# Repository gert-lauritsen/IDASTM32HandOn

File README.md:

På dette seminar vil vi sætte dig i gang med STM32. Vi ser på de værktøjer, du skal bruge for at komme i gang. Det hele er gratis, så det er bare med at komme i gang. Vi gennemgår alle basale hardwaredele, så du nemt kan komme videre. Der bliver nogle hands-on-opgaver, så tag din bærbare computer med.

Agenda

* Grafisk opsætning
* Debugger
* Seriel kommunikation (uart)
* SPI
* Timer
* ADC
* USB (virtuel comport)

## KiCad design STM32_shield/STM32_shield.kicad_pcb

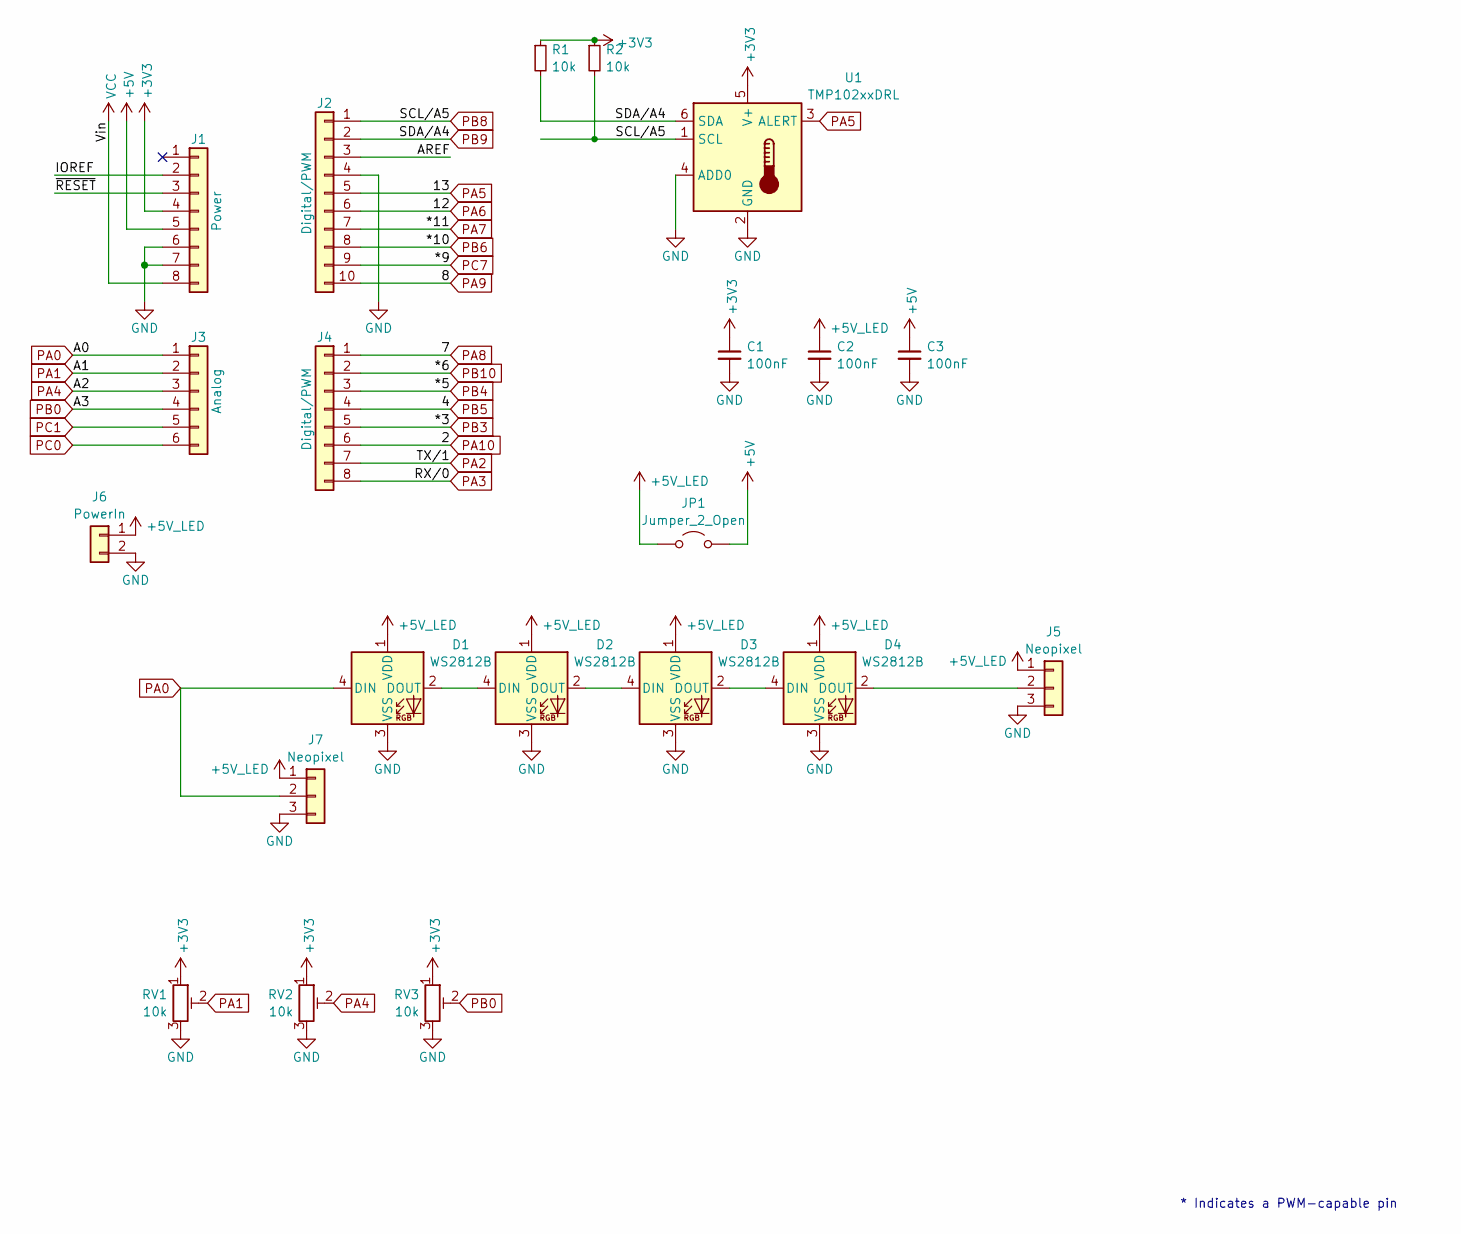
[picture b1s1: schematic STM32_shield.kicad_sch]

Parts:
C1, C2, C3: 100nF; C_0805_2012Metric
D1, D2, D3, D4: WS2812B; LED_WS2812B_PLCC4_5.0x5.0mm_P3.2mm; LCSC C114587
J1: Power; PinSocket_1x08_P2.54mm_Vertical
J2: Digital/PWM; PinSocket_1x10_P2.54mm_Vertical
J3: Analog; PinSocket_1x06_P2.54mm_Vertical
J4: Digital/PWM; PinSocket_1x08_P2.54mm_Vertical
J5, J7: Neopixel; PinSocket_1x03_P2.54mm_Vertical
J6: PowerIn; PhoenixContact_MSTBVA_2,5_2-G_1x02_P5.00mm_Vertical
JP1: Jumper_2_Open; SolderJumper-2_P1.3mm_Open_RoundedPad1.0x1.5mm
R1, R2: 10k; R_0805_2012Metric
RV1, RV2, RV3: 10k; Potentiometer_Runtron_RM-065_Vertical
U1: TMP102xxDRL; SOT-563; LCSC C99269

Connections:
+3V3: C1.1, J1.4, R1.1, R2.1, RV1.1, RV2.1, RV3.1, U1.5 (V+)
+5V: C3.1, J1.5, JP1.2 (B)
+5V_LED: C2.1, D1.1 (VDD), D2.1 (VDD), D3.1 (VDD), D4.1 (VDD), J5.1, J6.1, J7.1, JP1.1 (A)
/AREF: J2.3
/IOREF: J1.2
/~RESET: J1.3
GND: C1.2, C2.2, C3.2, D1.3 (VSS), D2.3 (VSS), D3.3 (VSS), D4.3 (VSS), J1.6, J1.7, J2.4, J5.3, J6.2, J7.3, RV1.3, RV2.3, RV3.3, U1.2 (GND), U1.4 (ADD0)
unnamed: D1.2 (DOUT), D2.4 (DIN)
unnamed: D2.2 (DOUT), D3.4 (DIN)
unnamed: D3.2 (DOUT), D4.4 (DIN)
unnamed: D4.2 (DOUT), J5.2
PA0: D1.4 (DIN), J3.1, J7.2
PA1: J3.2, RV1.2
PA2: J4.7
PA3: J4.8
PA4: J3.3, RV2.2
PA5: J2.5, U1.3 (ALERT)
PA6: J2.6
PA7: J2.7
PA8: J4.1
PA9: J2.10
PA10: J4.6
PB0: J3.4, RV3.2
PB3: J4.5
PB4: J4.3
PB5: J4.4
PB6: J2.8
PB8: J2.1, R2.2, U1.1 (SCL)
PB9: J2.2, R1.2, U1.6 (SDA)
PB10: J4.2
PC0: J3.6
PC1: J3.5
PC7: J2.9
VCC: J1.8

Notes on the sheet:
* Indicates a PWM-capable pin

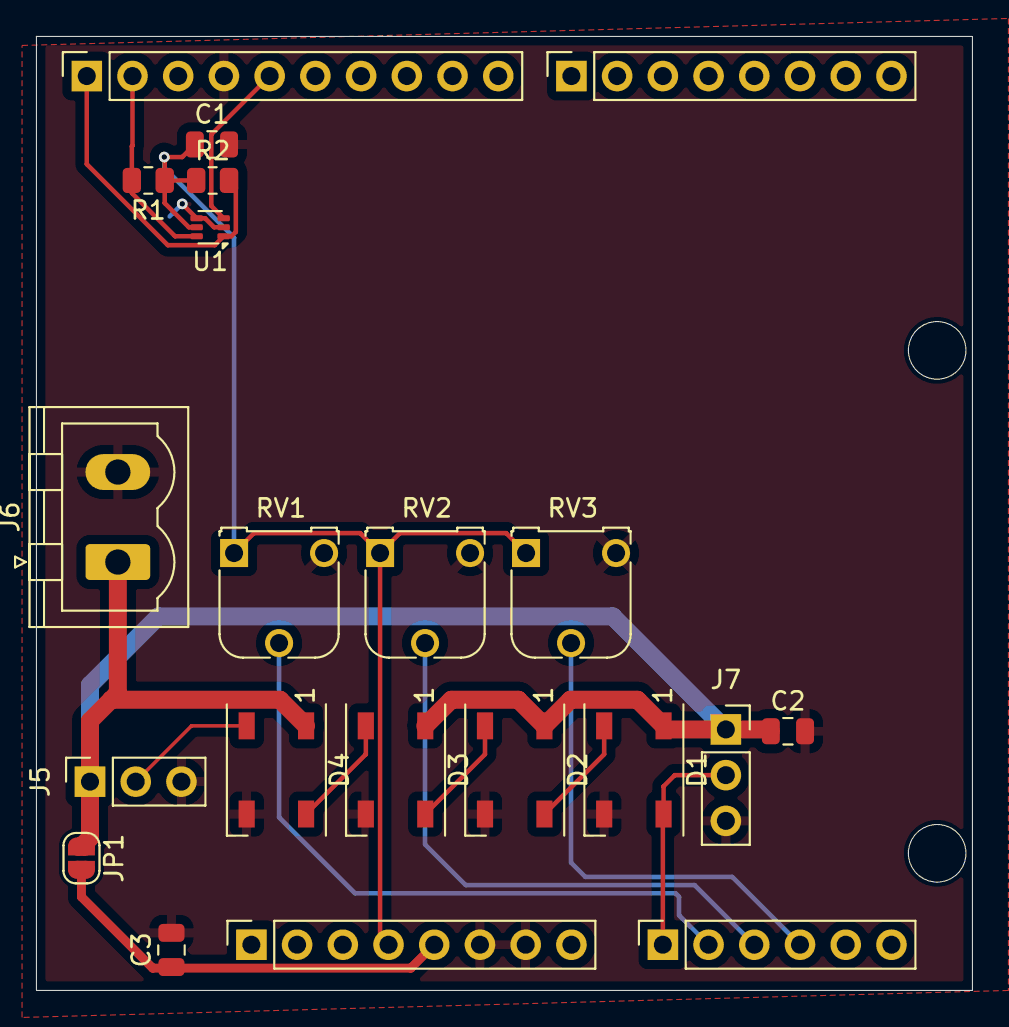
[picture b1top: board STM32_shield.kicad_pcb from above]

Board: 2 copper layers, 52.0 x 53.0 mm, 23 parts (0 on the bottom side), 15 nets.

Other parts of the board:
MH3, MH4: MountingHole_3.2mm

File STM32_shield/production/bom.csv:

Designator,Footprint,Quantity,Value,LCSC Part #
"C1, C2, C3",0805,3,100nF,
"D1, D2, D3, D4",LED_WS2812B_PLCC4_5.0x5.0mm_P3.2mm,4,WS2812B,C114587
J1,PinSocket_1x08_P2.54mm_Vertical,1,Power,
J2,PinSocket_1x10_P2.54mm_Vertical,1,Digital/PWM,
J3,PinSocket_1x06_P2.54mm_Vertical,1,Analog,
J4,PinSocket_1x08_P2.54mm_Vertical,1,Digital/PWM,
"J5, J7",PinSocket_1x03_P2.54mm_Vertical,2,Neopixel,
J6,"PhoenixContact_MSTBVA_2,5_2-G_1x02_P5.00mm_Vertical",1,PowerIn,
JP1,SolderJumper-2_P1.3mm_Open_RoundedPad1.0x1.5mm,1,Jumper_2_Open,
"R1, R2",0805,2,10k,
"RV1, RV2, RV3",Potentiometer_Runtron_RM-065_Vertical,3,10k,
U1,SOT-563,1,TMP102xxDRL,C99269

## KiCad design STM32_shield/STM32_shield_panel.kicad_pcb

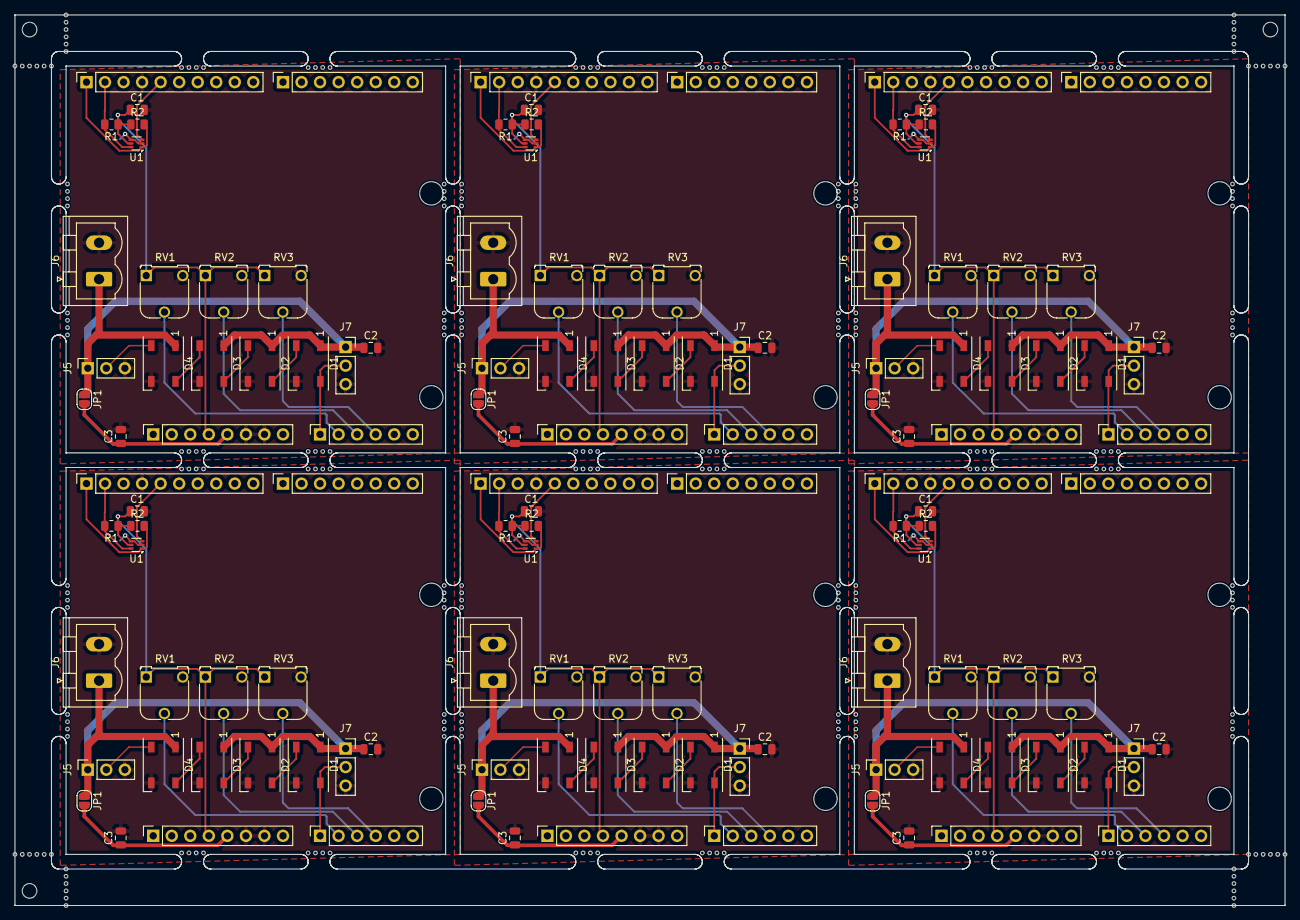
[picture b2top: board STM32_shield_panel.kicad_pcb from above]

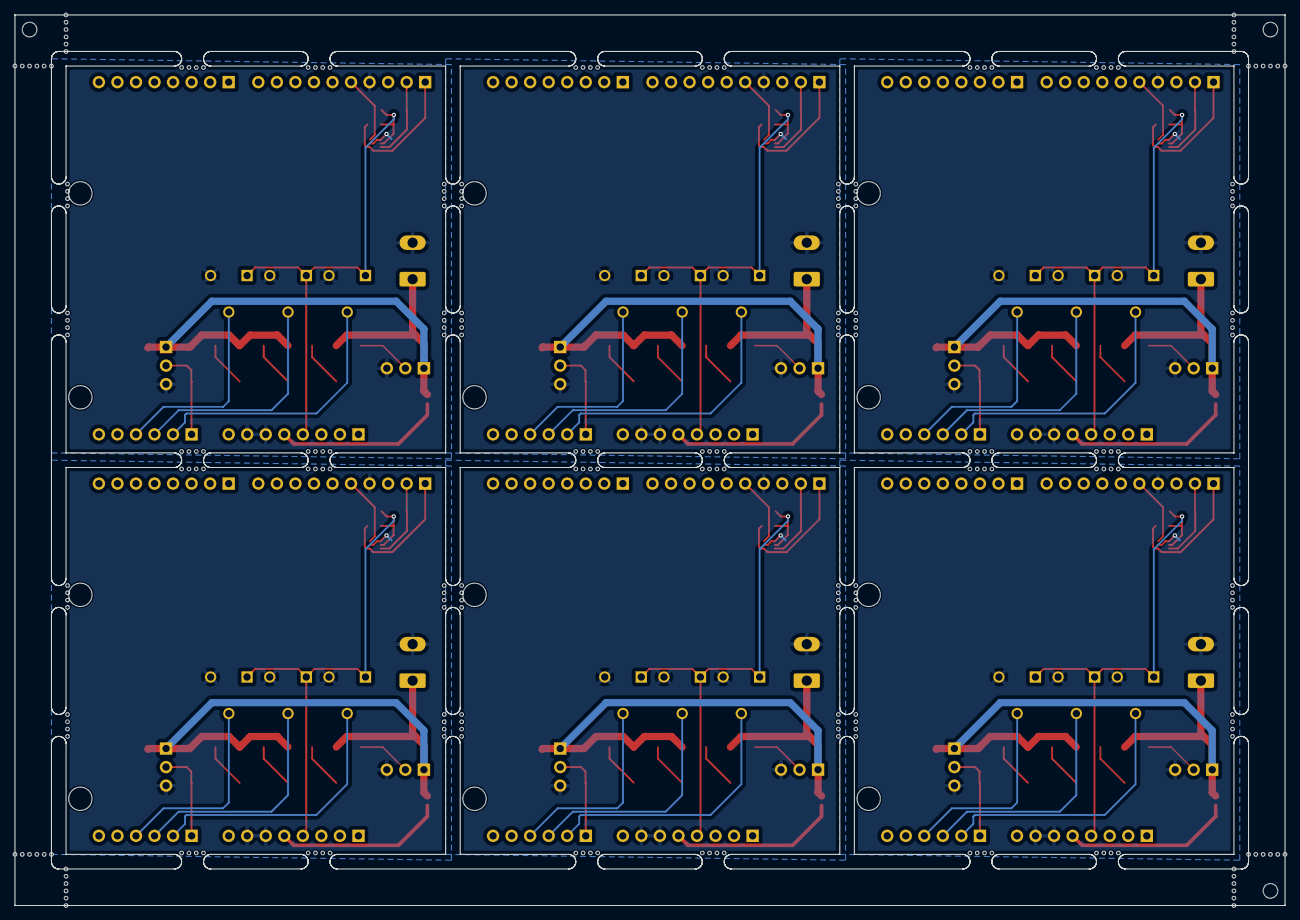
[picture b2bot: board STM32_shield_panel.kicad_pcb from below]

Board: 2 copper layers, 174.0 x 122.0 mm, 387 parts (3 on the bottom side), 90 nets.

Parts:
C1, C1#2, C1#3, C1#4, C1#5, C1#6, C2, C2#2, C2#3, C2#4, C2#5, C2#6, C3, C3#2, C3#3, C3#4, C3#5, C3#6: 100nF; C_0805_2012Metric
D1, D1#2, D1#3, D1#4, D1#5, D1#6, D2, D2#2, D2#3, D2#4, D2#5, D2#6, D3, D3#2, D3#3, D3#4, D3#5, D3#6, D4, D4#2, D4#3, D4#4, D4#5, D4#6: WS2812B; LED_WS2812B_PLCC4_5.0x5.0mm_P3.2mm
J1, J1#2, J1#3, J1#4, J1#5, J1#6: Power; PinSocket_1x08_P2.54mm_Vertical
J2, J2#2, J2#3, J2#4, J2#5, J2#6: Digital/PWM; PinSocket_1x10_P2.54mm_Vertical
J3, J3#2, J3#3, J3#4, J3#5, J3#6: Analog; PinSocket_1x06_P2.54mm_Vertical
J4, J4#2, J4#3, J4#4, J4#5, J4#6: Digital/PWM; PinSocket_1x08_P2.54mm_Vertical
J5, J5#2, J5#3, J5#4, J5#5, J5#6, J7, J7#2, J7#3, J7#4, J7#5, J7#6: Neopixel; PinSocket_1x03_P2.54mm_Vertical
J6, J6#2, J6#3, J6#4, J6#5, J6#6: PowerIn; PhoenixContact_MSTBVA_2,5_2-G_1x02_P5.00mm_Vertical
JP1, JP1#2, JP1#3, JP1#4, JP1#5, JP1#6: Jumper_2_Open; SolderJumper-2_P1.3mm_Open_RoundedPad1.0x1.5mm
KiKit_FID_B_1, KiKit_FID_B_2, KiKit_FID_B_3: Fiducial
KiKit_FID_T_1, KiKit_FID_T_2, KiKit_FID_T_3: Fiducial
KiKit_MB_1_1, KiKit_MB_1_2, KiKit_MB_1_3, KiKit_MB_1_4, KiKit_MB_2_1, KiKit_MB_2_2, KiKit_MB_2_3, KiKit_MB_2_4, KiKit_MB_3_1, KiKit_MB_3_2, KiKit_MB_3_3, KiKit_MB_3_4, KiKit_MB_4_1, KiKit_MB_4_2, KiKit_MB_4_3, KiKit_MB_4_4, KiKit_MB_5_1, KiKit_MB_5_2, KiKit_MB_5_3, KiKit_MB_5_4, KiKit_MB_6_1, KiKit_MB_6_2, KiKit_MB_6_3, KiKit_MB_6_4, KiKit_MB_7_1, KiKit_MB_7_2, KiKit_MB_7_3, KiKit_MB_7_4, KiKit_MB_8_1, KiKit_MB_8_2, KiKit_MB_8_3, KiKit_MB_8_4, KiKit_MB_9_1, KiKit_MB_9_2, KiKit_MB_9_3, KiKit_MB_9_4, KiKit_MB_10_1, KiKit_MB_10_2, KiKit_MB_10_3, KiKit_MB_10_4, KiKit_MB_11_1, KiKit_MB_11_2, KiKit_MB_11_3, KiKit_MB_11_4, KiKit_MB_12_1, KiKit_MB_12_2, KiKit_MB_12_3, KiKit_MB_12_4, KiKit_MB_13_1, KiKit_MB_13_2, KiKit_MB_13_3, KiKit_MB_13_4, KiKit_MB_14_1, KiKit_MB_14_2, KiKit_MB_14_3, KiKit_MB_14_4, KiKit_MB_15_1, KiKit_MB_15_2, KiKit_MB_15_3, KiKit_MB_15_4, KiKit_MB_16_1, KiKit_MB_16_2, KiKit_MB_16_3, KiKit_MB_16_4, KiKit_MB_17_1, KiKit_MB_17_2, KiKit_MB_17_3, KiKit_MB_17_4, KiKit_MB_18_1, KiKit_MB_18_2, KiKit_MB_18_3, KiKit_MB_18_4, KiKit_MB_19_1, KiKit_MB_19_2, KiKit_MB_19_3, KiKit_MB_19_4, KiKit_MB_20_1, KiKit_MB_20_2, KiKit_MB_20_3, KiKit_MB_20_4, KiKit_MB_21_1, KiKit_MB_21_2, KiKit_MB_21_3, KiKit_MB_21_4, KiKit_MB_22_1, KiKit_MB_22_2, KiKit_MB_22_3, KiKit_MB_22_4, KiKit_MB_23_1, KiKit_MB_23_2, KiKit_MB_23_3, KiKit_MB_23_4, KiKit_MB_24_1, KiKit_MB_24_2, KiKit_MB_24_3, KiKit_MB_24_4, KiKit_MB_25_1, KiKit_MB_25_2, KiKit_MB_25_3, KiKit_MB_25_4, KiKit_MB_26_1, KiKit_MB_26_2, KiKit_MB_26_3, KiKit_MB_26_4, KiKit_MB_27_1, KiKit_MB_27_2, KiKit_MB_27_3, KiKit_MB_27_4, KiKit_MB_28_1, KiKit_MB_28_2, KiKit_MB_28_3, KiKit_MB_28_4, KiKit_MB_29_1, KiKit_MB_29_2, KiKit_MB_29_3, KiKit_MB_29_4, KiKit_MB_30_1, KiKit_MB_30_2, KiKit_MB_30_3, KiKit_MB_30_4, KiKit_MB_31_1, KiKit_MB_31_2, KiKit_MB_31_3, KiKit_MB_31_4, KiKit_MB_32_1, KiKit_MB_32_2, KiKit_MB_32_3, KiKit_MB_32_4, KiKit_MB_33_1, KiKit_MB_33_2, KiKit_MB_33_3, KiKit_MB_33_4, KiKit_MB_34_1, KiKit_MB_34_2, KiKit_MB_34_3, KiKit_MB_34_4, KiKit_MB_35_1, KiKit_MB_35_2, KiKit_MB_35_3, KiKit_MB_35_4, KiKit_MB_36_1, KiKit_MB_36_2, KiKit_MB_36_3, KiKit_MB_36_4, KiKit_MB_37_1, KiKit_MB_37_2, KiKit_MB_37_3, KiKit_MB_37_4, KiKit_MB_38_1, KiKit_MB_38_2, KiKit_MB_38_3, KiKit_MB_38_4, KiKit_MB_39_1, KiKit_MB_39_2, KiKit_MB_39_3, KiKit_MB_39_4, KiKit_MB_40_1, KiKit_MB_40_2, KiKit_MB_40_3, KiKit_MB_40_4, KiKit_MB_41_1, KiKit_MB_41_2, KiKit_MB_41_3, KiKit_MB_41_4, KiKit_MB_42_1, KiKit_MB_42_2, KiKit_MB_42_3, KiKit_MB_42_4, KiKit_MB_43_1, KiKit_MB_43_2, KiKit_MB_43_3, KiKit_MB_43_4, KiKit_MB_44_1, KiKit_MB_44_2, KiKit_MB_44_3, KiKit_MB_44_4, KiKit_MB_45_1, KiKit_MB_45_2, KiKit_MB_45_3, KiKit_MB_45_4, KiKit_MB_46_1, KiKit_MB_46_2, KiKit_MB_46_3, KiKit_MB_46_4, KiKit_MB_47_1, KiKit_MB_47_2, KiKit_MB_47_3, KiKit_MB_47_4, KiKit_MB_48_1, KiKit_MB_48_2, KiKit_MB_48_3, KiKit_MB_48_4, KiKit_MB_49_1, KiKit_MB_49_2, KiKit_MB_49_3, KiKit_MB_49_4, KiKit_MB_49_5, KiKit_MB_49_6, KiKit_MB_50_1, KiKit_MB_50_2, KiKit_MB_50_3, KiKit_MB_50_4, KiKit_MB_50_5, KiKit_MB_50_6, KiKit_MB_51_1, KiKit_MB_51_2, KiKit_MB_51_3, KiKit_MB_51_4, KiKit_MB_51_5, KiKit_MB_51_6, KiKit_MB_52_1, KiKit_MB_52_2, KiKit_MB_52_3, KiKit_MB_52_4, KiKit_MB_52_5, KiKit_MB_52_6, KiKit_MB_53_1, KiKit_MB_53_2, KiKit_MB_53_3, KiKit_MB_53_4, KiKit_MB_53_5, KiKit_MB_53_6, KiKit_MB_54_1, KiKit_MB_54_2, KiKit_MB_54_3, KiKit_MB_54_4, KiKit_MB_54_5, KiKit_MB_54_6, KiKit_MB_55_1, KiKit_MB_55_2, KiKit_MB_55_3, KiKit_MB_55_4, KiKit_MB_55_5, KiKit_MB_55_6, KiKit_MB_56_1, KiKit_MB_56_2, KiKit_MB_56_3, KiKit_MB_56_4, KiKit_MB_56_5, KiKit_MB_56_6: NPTH
KiKit_TO_1, KiKit_TO_2, KiKit_TO_3: NPTH
MH3, MH3#2, MH3#3, MH3#4, MH3#5, MH3#6, MH4, MH4#2, MH4#3, MH4#4, MH4#5, MH4#6: MountingHole_3.2mm
R1, R1#2, R1#3, R1#4, R1#5, R1#6, R2, R2#2, R2#3, R2#4, R2#5, R2#6: 10k; R_0805_2012Metric
RV1, RV1#2, RV1#3, RV1#4, RV1#5, RV1#6, RV2, RV2#2, RV2#3, RV2#4, RV2#5, RV2#6, RV3, RV3#2, RV3#3, RV3#4, RV3#5, RV3#6: 10k; Potentiometer_Runtron_RM-065_Vertical
U1, U1#2, U1#3, U1#4, U1#5, U1#6: TMP102xxDRL; SOT-563

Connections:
Board_0-+3V3: C1.1, J1#6.4, R1#5.1, R2#6.1, RV1.1, RV2.1, RV3#5.1, U1#6.5 (V+)
Board_0-+5V: C3#5.1, J1#6.5, JP1#5.2 (B)
Board_0-+5V_LED: C2#6.1, D1.1 (VDD), D2.1 (VDD), D3#4.1 (VDD), D4#6.1 (VDD), J5#3.1, J6#6.1, J7.1, JP1#5.1 (A)
Board_0-GND: C1.2, C2#6.2, C3#5.2, D1.3 (VSS), D2.3 (VSS), D3#4.3 (VSS), D4#6.3 (VSS), J1#6.6, J1#6.7, J2#5.4, J5#3.3, J6#6.2, J7.3, RV1.3, RV2.3, RV3#5.3, U1#6.2 (GND), U1#6.4 (ADD0)
Board_0-Net-(D1-DOUT): D1.2 (DOUT), D2.4 (DIN)
Board_0-Net-(D2-DOUT): D2.2 (DOUT), D3#4.4 (DIN)
Board_0-Net-(D3-DOUT): D3#4.2 (DOUT), D4#6.4 (DIN)
Board_0-Net-(D4-DOUT): D4#6.2 (DOUT), J5#3.2
Board_0-PA0: D1.4 (DIN), J3.1, J7.2
Board_0-PA1: J3.2, RV1.2
Board_0-PA4: J3.3, RV2.2
Board_0-PA5: J2#5.5, U1#6.3 (ALERT)
Board_0-PB0: J3.4, RV3#5.2
Board_0-PB8: J2#5.1, R2#6.2, U1#6.1 (SCL)
Board_0-PB9: J2#5.2, R1#5.2, U1#6.6 (SDA)
Board_1-+3V3: C1#2.1, J1#3.4, R1#2.1, R2#3.1, RV1#4.1, RV2#4.1, RV3.1, U1#4.5 (V+)
Board_1-+5V: C3#3.1, J1#3.5, JP1#2.2 (B)
Board_1-+5V_LED: C2#3.1, D1#6.1 (VDD), D2#4.1 (VDD), D3#5.1 (VDD), D4#5.1 (VDD), J5#2.1, J6#3.1, J7#2.1, JP1#2.1 (A)
Board_1-GND: C1#2.2, C2#3.2, C3#3.2, D1#6.3 (VSS), D2#4.3 (VSS), D3#5.3 (VSS), D4#5.3 (VSS), J1#3.6, J1#3.7, J2#2.4, J5#2.3, J6#3.2, J7#2.3, RV1#4.3, RV2#4.3, RV3.3, U1#4.2 (GND), U1#4.4 (ADD0)
Board_1-Net-(D1-DOUT): D1#6.2 (DOUT), D2#4.4 (DIN)
Board_1-Net-(D2-DOUT): D2#4.2 (DOUT), D3#5.4 (DIN)
Board_1-Net-(D3-DOUT): D3#5.2 (DOUT), D4#5.4 (DIN)
Board_1-Net-(D4-DOUT): D4#5.2 (DOUT), J5#2.2
Board_1-PA0: D1#6.4 (DIN), J3#5.1, J7#2.2
Board_1-PA1: J3#5.2, RV1#4.2
Board_1-PA4: J3#5.3, RV2#4.2
Board_1-PA5: J2#2.5, U1#4.3 (ALERT)
Board_1-PB0: J3#5.4, RV3.2
Board_1-PB8: J2#2.1, R2#3.2, U1#4.1 (SCL)
Board_1-PB9: J2#2.2, R1#2.2, U1#4.6 (SDA)
Board_2-+3V3: C1#3.1, J1#4.4, R1#4.1, R2#5.1, RV1#3.1, RV2#2.1, RV3#6.1, U1#3.5 (V+)
Board_2-+5V: C3#4.1, J1#4.5, JP1.2 (B)
Board_2-+5V_LED: C2#5.1, D1#3.1 (VDD), D2#2.1 (VDD), D3#3.1 (VDD), D4#3.1 (VDD), J5#6.1, J6#4.1, J7#4.1, JP1.1 (A)
Board_2-GND: C1#3.2, C2#5.2, C3#4.2, D1#3.3 (VSS), D2#2.3 (VSS), D3#3.3 (VSS), D4#3.3 (VSS), J1#4.6, J1#4.7, J2#6.4, J5#6.3, J6#4.2, J7#4.3, RV1#3.3, RV2#2.3, RV3#6.3, U1#3.2 (GND), U1#3.4 (ADD0)
Board_2-Net-(D1-DOUT): D1#3.2 (DOUT), D2#2.4 (DIN)
Board_2-Net-(D2-DOUT): D2#2.2 (DOUT), D3#3.4 (DIN)
Board_2-Net-(D3-DOUT): D3#3.2 (DOUT), D4#3.4 (DIN)
Board_2-Net-(D4-DOUT): D4#3.2 (DOUT), J5#6.2
Board_2-PA0: D1#3.4 (DIN), J3#2.1, J7#4.2
Board_2-PA1: J3#2.2, RV1#3.2
Board_2-PA4: J3#2.3, RV2#2.2
Board_2-PA5: J2#6.5, U1#3.3 (ALERT)
Board_2-PB0: J3#2.4, RV3#6.2
Board_2-PB8: J2#6.1, R2#5.2, U1#3.1 (SCL)
Board_2-PB9: J2#6.2, R1#4.2, U1#3.6 (SDA)
Board_3-+3V3: C1#4.1, J1#2.4, R1.1, R2#2.1, RV1#6.1, RV2#3.1, RV3#3.1, U1#5.5 (V+)
Board_3-+5V: C3#2.1, J1#2.5, JP1#4.2 (B)
Board_3-+5V_LED: C2#2.1, D1#4.1 (VDD), D2#5.1 (VDD), D3#6.1 (VDD), D4#2.1 (VDD), J5.1, J6#5.1, J7#5.1, JP1#4.1 (A)
Board_3-GND: C1#4.2, C2#2.2, C3#2.2, D1#4.3 (VSS), D2#5.3 (VSS), D3#6.3 (VSS), D4#2.3 (VSS), J1#2.6, J1#2.7, J2#3.4, J5.3, J6#5.2, J7#5.3, RV1#6.3, RV2#3.3, RV3#3.3, U1#5.2 (GND), U1#5.4 (ADD0)
Board_3-Net-(D1-DOUT): D1#4.2 (DOUT), D2#5.4 (DIN)
Board_3-Net-(D2-DOUT): D2#5.2 (DOUT), D3#6.4 (DIN)
Board_3-Net-(D3-DOUT): D3#6.2 (DOUT), D4#2.4 (DIN)
Board_3-Net-(D4-DOUT): D4#2.2 (DOUT), J5.2
Board_3-PA0: D1#4.4 (DIN), J3#4.1, J7#5.2
Board_3-PA1: J3#4.2, RV1#6.2
Board_3-PA4: J3#4.3, RV2#3.2
Board_3-PA5: J2#3.5, U1#5.3 (ALERT)
Board_3-PB0: J3#4.4, RV3#3.2
Board_3-PB8: J2#3.1, R2#2.2, U1#5.1 (SCL)
Board_3-PB9: J2#3.2, R1.2, U1#5.6 (SDA)
Board_4-+3V3: C1#5.1, J1.4, R1#6.1, R2#4.1, RV1#5.1, RV2#5.1, RV3#4.1, U1.5 (V+)
Board_4-+5V: C3.1, J1.5, JP1#3.2 (B)
Board_4-+5V_LED: C2#4.1, D1#2.1 (VDD), D2#6.1 (VDD), D3#2.1 (VDD), D4#4.1 (VDD), J5#4.1, J6.1, J7#3.1, JP1#3.1 (A)
Board_4-GND: C1#5.2, C2#4.2, C3.2, D1#2.3 (VSS), D2#6.3 (VSS), D3#2.3 (VSS), D4#4.3 (VSS), J1.6, J1.7, J2.4, J5#4.3, J6.2, J7#3.3, RV1#5.3, RV2#5.3, RV3#4.3, U1.2 (GND), U1.4 (ADD0)
Board_4-Net-(D1-DOUT): D1#2.2 (DOUT), D2#6.4 (DIN)
Board_4-Net-(D2-DOUT): D2#6.2 (DOUT), D3#2.4 (DIN)
Board_4-Net-(D3-DOUT): D3#2.2 (DOUT), D4#4.4 (DIN)
Board_4-Net-(D4-DOUT): D4#4.2 (DOUT), J5#4.2
Board_4-PA0: D1#2.4 (DIN), J3#6.1, J7#3.2
Board_4-PA1: J3#6.2, RV1#5.2
Board_4-PA4: J3#6.3, RV2#5.2
Board_4-PA5: J2.5, U1.3 (ALERT)
Board_4-PB0: J3#6.4, RV3#4.2
Board_4-PB8: J2.1, R2#4.2, U1.1 (SCL)
Board_4-PB9: J2.2, R1#6.2, U1.6 (SDA)
Board_5-+3V3: C1#6.1, J1#5.4, R1#3.1, R2.1, RV1#2.1, RV2#6.1, RV3#2.1, U1#2.5 (V+)
Board_5-+5V: C3#6.1, J1#5.5, JP1#6.2 (B)
Board_5-+5V_LED: C2.1, D1#5.1 (VDD), D2#3.1 (VDD), D3.1 (VDD), D4.1 (VDD), J5#5.1, J6#2.1, J7#6.1, JP1#6.1 (A)
Board_5-GND: C1#6.2, C2.2, C3#6.2, D1#5.3 (VSS), D2#3.3 (VSS), D3.3 (VSS), D4.3 (VSS), J1#5.6, J1#5.7, J2#4.4, J5#5.3, J6#2.2, J7#6.3, RV1#2.3, RV2#6.3, RV3#2.3, U1#2.2 (GND), U1#2.4 (ADD0)
Board_5-Net-(D1-DOUT): D1#5.2 (DOUT), D2#3.4 (DIN)
Board_5-Net-(D2-DOUT): D2#3.2 (DOUT), D3.4 (DIN)
Board_5-Net-(D3-DOUT): D3.2 (DOUT), D4.4 (DIN)
Board_5-Net-(D4-DOUT): D4.2 (DOUT), J5#5.2
Board_5-PA0: D1#5.4 (DIN), J3#3.1, J7#6.2
Board_5-PA1: J3#3.2, RV1#2.2
Board_5-PA4: J3#3.3, RV2#6.2
Board_5-PA5: J2#4.5, U1#2.3 (ALERT)
Board_5-PB0: J3#3.4, RV3#2.2
Board_5-PB8: J2#4.1, R2.2, U1#2.1 (SCL)
Board_5-PB9: J2#4.2, R1#3.2, U1#2.6 (SDA)

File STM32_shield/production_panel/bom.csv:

Designator,Footprint,Quantity,Value,LCSC Part #
"C1_6, C1_5, C1_4, C1_3, C1_2, C1, C2_6, C2_5, C2_4, C2_3, C2_2, C2, C3_6, C3_5, C3_4, C3_3, C3_2, C3",0805,18,100nF,
"D1_6, D1_5, D1_4, D1_3, D1_2, D1, D2_6, D2_5, D2_4, D2_3, D2_2, D2, D3_6, D3_5, D3_4, D3_3, D3_2, D3, D4_6, D4_5, D4_4, D4_3, D4_2, D4",LED_WS2812B_PLCC4_5.0x5.0mm_P3.2mm,24,WS2812B,C114587
"J1_6, J1_5, J1_4, J1_3, J1_2, J1",PinSocket_1x08_P2.54mm_Vertical,6,Power,
"J2_6, J2_5, J2_4, J2_3, J2_2, J2",PinSocket_1x10_P2.54mm_Vertical,6,Digital/PWM,
"J3_6, J3_5, J3_4, J3_3, J3_2, J3",PinSocket_1x06_P2.54mm_Vertical,6,Analog,
"J4_6, J4_5, J4_4, J4_3, J4_2, J4",PinSocket_1x08_P2.54mm_Vertical,6,Digital/PWM,
"J5_6, J5_5, J5_4, J5_3, J5_2, J5, J7_6, J7_5, J7_4, J7_3, J7_2, J7",PinSocket_1x03_P2.54mm_Vertical,12,Neopixel,
"J6_6, J6_5, J6_4, J6_3, J6_2, J6","PhoenixContact_MSTBVA_2,5_2-G_1x02_P5.00mm_Vertical",6,PowerIn,
"JP1_6, JP1_5, JP1_4, JP1_3, JP1_2, JP1",SolderJumper-2_P1.3mm_Open_RoundedPad1.0x1.5mm,6,Jumper_2_Open,
"KiKit_FID_B_1, KiKit_FID_B_2, KiKit_FID_B_3, KiKit_FID_T_1, KiKit_FID_T_2, KiKit_FID_T_3",Fiducial,6,Fiducial,
"KiKit_MB_10_1, KiKit_MB_10_2, KiKit_MB_10_3, KiKit_MB_10_4, KiKit_MB_11_1, KiKit_MB_11_2, KiKit_MB_11_3, KiKit_MB_11_4, KiKit_MB_12_1, KiKit_MB_12_2, KiKit_MB_12_3, KiKit_MB_12_4, KiKit_MB_13_1, KiKit_MB_13_2, KiKit_MB_13_3, KiKit_MB_13_4, KiKit_MB_14_1, KiKit_MB_14_2, KiKit_MB_14_3, KiKit_MB_14_4, KiKit_MB_15_1, KiKit_MB_15_2, KiKit_MB_15_3, KiKit_MB_15_4, KiKit_MB_16_1, KiKit_MB_16_2, KiKit_MB_16_3, KiKit_MB_16_4, KiKit_MB_17_1, KiKit_MB_17_2, KiKit_MB_17_3, KiKit_MB_17_4, KiKit_MB_18_1, KiKit_MB_18_2, KiKit_MB_18_3, KiKit_MB_18_4, KiKit_MB_19_1, KiKit_MB_19_2, KiKit_MB_19_3, KiKit_MB_19_4, KiKit_MB_1_1, KiKit_MB_1_2, KiKit_MB_1_3, KiKit_MB_1_4, KiKit_MB_20_1, KiKit_MB_20_2, KiKit_MB_20_3, KiKit_MB_20_4, KiKit_MB_21_1, KiKit_MB_21_2, KiKit_MB_21_3, KiKit_MB_21_4, KiKit_MB_22_1, KiKit_MB_22_2, KiKit_MB_22_3, KiKit_MB_22_4, KiKit_MB_23_1, KiKit_MB_23_2, KiKit_MB_23_3, KiKit_MB_23_4, KiKit_MB_24_1, KiKit_MB_24_2, KiKit_MB_24_3, KiKit_MB_24_4, KiKit_MB_25_1, KiKit_MB_25_2, KiKit_MB_25_3, KiKit_MB_25_4, KiKit_MB_26_1, KiKit_MB_26_2, KiKit_MB_26_3, KiKit_MB_26_4, KiKit_MB_27_1, KiKit_MB_27_2, KiKit_MB_27_3, KiKit_MB_27_4, KiKit_MB_28_1, KiKit_MB_28_2, KiKit_MB_28_3, KiKit_MB_28_4, KiKit_MB_29_1, KiKit_MB_29_2, KiKit_MB_29_3, KiKit_MB_29_4, KiKit_MB_2_1, KiKit_MB_2_2, KiKit_MB_2_3, KiKit_MB_2_4, KiKit_MB_30_1, KiKit_MB_30_2, KiKit_MB_30_3, KiKit_MB_30_4, KiKit_MB_31_1, KiKit_MB_31_2, KiKit_MB_31_3, KiKit_MB_31_4, KiKit_MB_32_1, KiKit_MB_32_2, KiKit_MB_32_3, KiKit_MB_32_4, KiKit_MB_33_1, KiKit_MB_33_2, KiKit_MB_33_3, KiKit_MB_33_4, KiKit_MB_34_1, KiKit_MB_34_2, KiKit_MB_34_3, KiKit_MB_34_4, KiKit_MB_35_1, KiKit_MB_35_2, KiKit_MB_35_3, KiKit_MB_35_4, KiKit_MB_36_1, KiKit_MB_36_2, KiKit_MB_36_3, KiKit_MB_36_4, KiKit_MB_37_1, KiKit_MB_37_2, KiKit_MB_37_3, KiKit_MB_37_4, KiKit_MB_38_1, KiKit_MB_38_2, KiKit_MB_38_3, KiKit_MB_38_4, KiKit_MB_39_1, KiKit_MB_39_2, KiKit_MB_39_3, KiKit_MB_39_4, KiKit_MB_3_1, KiKit_MB_3_2, KiKit_MB_3_3, KiKit_MB_3_4, KiKit_MB_40_1, KiKit_MB_40_2, KiKit_MB_40_3, KiKit_MB_40_4, KiKit_MB_41_1, KiKit_MB_41_2, KiKit_MB_41_3, KiKit_MB_41_4, KiKit_MB_42_1, KiKit_MB_42_2, KiKit_MB_42_3, KiKit_MB_42_4, KiKit_MB_43_1, KiKit_MB_43_2, KiKit_MB_43_3, KiKit_MB_43_4, KiKit_MB_44_1, KiKit_MB_44_2, KiKit_MB_44_3, KiKit_MB_44_4, KiKit_MB_45_1, KiKit_MB_45_2, KiKit_MB_45_3, KiKit_MB_45_4, KiKit_MB_46_1, KiKit_MB_46_2, KiKit_MB_46_3, KiKit_MB_46_4, KiKit_MB_47_1, KiKit_MB_47_2, KiKit_MB_47_3, KiKit_MB_47_4, KiKit_MB_48_1, KiKit_MB_48_2, KiKit_MB_48_3, KiKit_MB_48_4, KiKit_MB_49_1, KiKit_MB_49_2, KiKit_MB_49_3, KiKit_MB_49_4, KiKit_MB_49_5, KiKit_MB_49_6, KiKit_MB_4_1, KiKit_MB_4_2, KiKit_MB_4_3, KiKit_MB_4_4, KiKit_MB_50_1, KiKit_MB_50_2, KiKit_MB_50_3, KiKit_MB_50_4, KiKit_MB_50_5, KiKit_MB_50_6, KiKit_MB_51_1, KiKit_MB_51_2, KiKit_MB_51_3, KiKit_MB_51_4, KiKit_MB_51_5, KiKit_MB_51_6, KiKit_MB_52_1, KiKit_MB_52_2, KiKit_MB_52_3, KiKit_MB_52_4, KiKit_MB_52_5, KiKit_MB_52_6, KiKit_MB_53_1, KiKit_MB_53_2, KiKit_MB_53_3, KiKit_MB_53_4",NPTH,200,NPTH,
"KiKit_MB_53_5, KiKit_MB_53_6, KiKit_MB_54_1, KiKit_MB_54_2, KiKit_MB_54_3, KiKit_MB_54_4, KiKit_MB_54_5, KiKit_MB_54_6, KiKit_MB_55_1, KiKit_MB_55_2, KiKit_MB_55_3, KiKit_MB_55_4, KiKit_MB_55_5, KiKit_MB_55_6, KiKit_MB_56_1, KiKit_MB_56_2, KiKit_MB_56_3, KiKit_MB_56_4, KiKit_MB_56_5, KiKit_MB_56_6, KiKit_MB_5_1, KiKit_MB_5_2, KiKit_MB_5_3, KiKit_MB_5_4, KiKit_MB_6_1, KiKit_MB_6_2, KiKit_MB_6_3, KiKit_MB_6_4, KiKit_MB_7_1, KiKit_MB_7_2, KiKit_MB_7_3, KiKit_MB_7_4, KiKit_MB_8_1, KiKit_MB_8_2, KiKit_MB_8_3, KiKit_MB_8_4, KiKit_MB_9_1, KiKit_MB_9_2, KiKit_MB_9_3, KiKit_MB_9_4, KiKit_TO_1, KiKit_TO_2, KiKit_TO_3",NPTH,43,NPTH,
"R1_6, R1_5, R1_4, R1_3, R1_2, R1, R2_6, R2_5, R2_4, R2_3, R2_2, R2",0805,12,10k,
"RV1_6, RV1_5, RV1_4, RV1_3, RV1_2, RV1, RV2_6, RV2_5, RV2_4, RV2_3, RV2_2, RV2, RV3_6, RV3_5, RV3_4, RV3_3, RV3_2, RV3",Potentiometer_Runtron_RM-065_Vertical,18,10k,
"U1_6, U1_5, U1_4, U1_3, U1_2, U1",SOT-563,6,TMP102xxDRL,C99269

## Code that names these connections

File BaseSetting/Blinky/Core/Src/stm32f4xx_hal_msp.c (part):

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
    __HAL_RCC_GPIOA_CLK_ENABLE();
    /**ADC1 GPIO Configuration
    PA1     ------> ADC1_IN1
    */
    GPIO_InitStruct.Pin = GPIO_PIN_1;
    GPIO_InitStruct.Mode = GPIO_MODE_ANALOG;
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    __HAL_RCC_ADC1_CLK_DISABLE();

    /**ADC1 GPIO Configuration
    PA1     ------> ADC1_IN1
    */
    HAL_GPIO_DeInit(GPIOA, GPIO_PIN_1);

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
    __HAL_RCC_GPIOB_CLK_ENABLE();
    /**I2C1 GPIO Configuration
    PB8     ------> I2C1_SCL
    PB9     ------> I2C1_SDA
    */
    GPIO_InitStruct.Pin = GPIO_PIN_8|GPIO_PIN_9;
    GPIO_InitStruct.Mode = GPIO_MODE_AF_OD;
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    __HAL_RCC_I2C1_CLK_DISABLE();

    /**I2C1 GPIO Configuration
    PB8     ------> I2C1_SCL
    PB9     ------> I2C1_SDA
    */
    HAL_GPIO_DeInit(GPIOB, GPIO_PIN_8);

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
    __HAL_RCC_GPIOA_CLK_ENABLE();
    /**TIM2 GPIO Configuration
    PA0-WKUP     ------> TIM2_CH1
    */
    GPIO_InitStruct.Pin = GPIO_PIN_0;
    GPIO_InitStruct.Mode = GPIO_MODE_AF_PP;
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
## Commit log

2024-05-22 Init
2024-05-22 Blinky added
2024-05-25 video added
2024-05-26 I2C test done
2024-05-27 neopixel added, not tested
2024-05-27 adc demo added
2024-05-27 USB demo
2024-05-27 Serial
2024-05-28 powerpoint update
2024-05-28 Neopixel
2024-05-28 powerpoint
2024-05-28 flytning af projecter til oprindeligt sted
2024-05-29 powerpoint
    powerpoint

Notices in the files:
BaseSetting/Blinky/Core/Src/stm32f4xx_hal_msp.c:
Copyright (c) 2024 STMicroelectronics.
All rights reserved.
This software is licensed under terms that can be found in the LICENSE file
